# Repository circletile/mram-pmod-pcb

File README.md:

# mram-pmod-pcb
A PMOD for interfacing with Everspin MRAM modules

Designed to add additinoal memory for an FPGA-based project I was working on. Everspin MRAM modules seemed interesting, so I built out a PMOD for it. Schematic and board designed using KiCad.

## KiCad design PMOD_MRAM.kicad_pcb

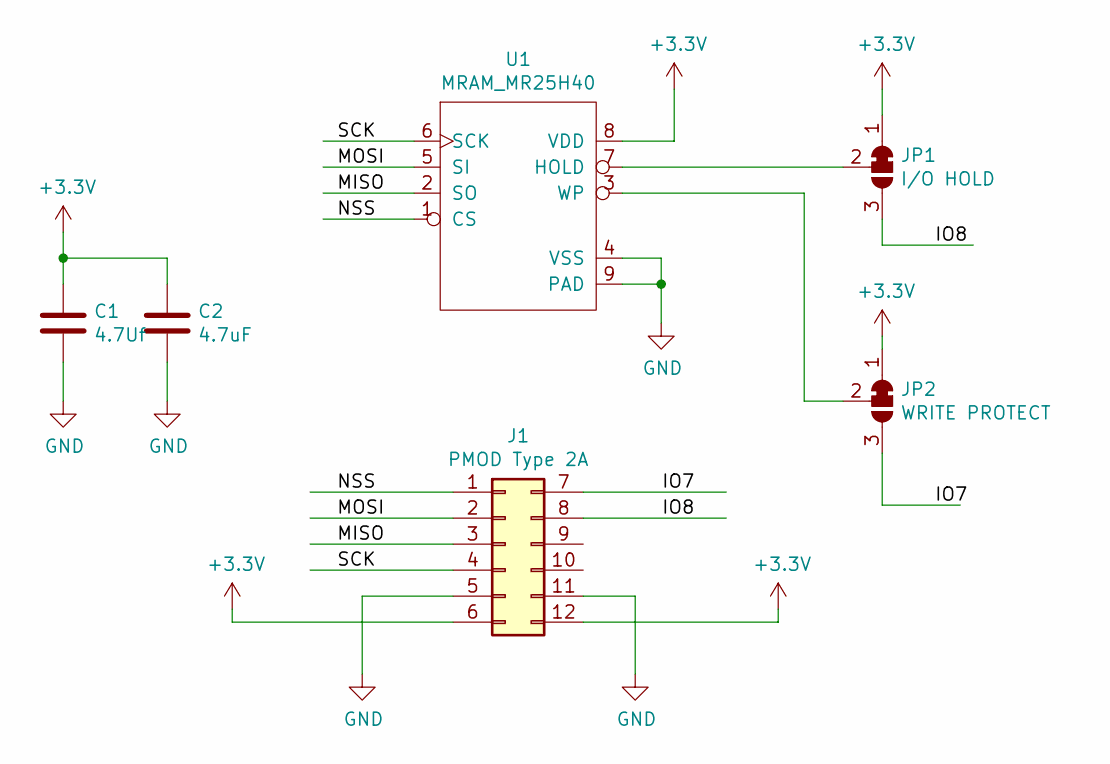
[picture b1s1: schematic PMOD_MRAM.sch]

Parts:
C1: 4.7Uf; C_0603_1608Metric_Pad1.08x0.95mm_HandSolder
C2: 4.7uF; C_0603_1608Metric_Pad1.08x0.95mm_HandSolder
J1: PMOD Type 2A; PMOD_PinHeader_2x06_P2.54mm_Horizontal
JP1: I/O HOLD; SolderJumper-3_P1.3mm_Bridged12_Pad1.0x1.5mm_NumberLabels
JP2: WRITE PROTECT; SolderJumper-3_P1.3mm_Bridged12_Pad1.0x1.5mm_NumberLabels
U1: MRAM_MR25H40; MR20H40_MR25H40_8DFN-SFP

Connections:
+3V3: C1.1, C2.1, J1.6, J1.12, JP1.1 (A), JP2.1 (A), U1.8 (VDD)
/IO7: J1.7, JP2.3 (B)
/IO8: J1.8, JP1.3 (B)
/MISO: J1.3, U1.2 (SO)
/MOSI: J1.2, U1.5 (SI)
/NSS: J1.1, U1.1 (CS)
/SCK: J1.4, U1.6 (SCK)
GND: C1.2, C2.2, J1.5, J1.11, U1.4 (VSS), U1.9 (PAD)
unnamed: JP1.2 (C), U1.7 (HOLD)
unnamed: JP2.2 (C), U1.3 (WP)

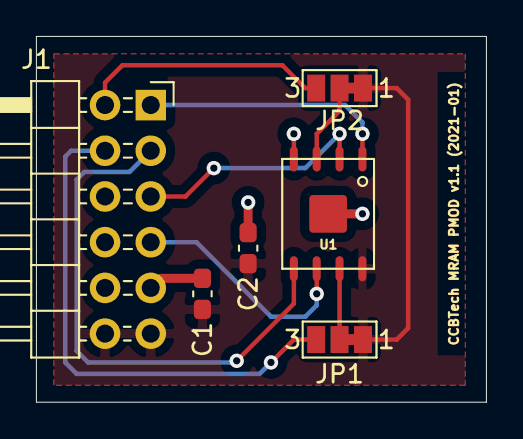
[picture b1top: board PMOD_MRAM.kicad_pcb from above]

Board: 2 copper layers, 25.0 x 20.3 mm, 6 parts (0 on the bottom side), 10 nets.
